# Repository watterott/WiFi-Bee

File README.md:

# WiFi-Bee
XBee footprint compatible WiFi/WLAN Module with Microchip ATWINC1500 WiFi Network Controller.

* [Microchip ATWINC1500](https://www.microchip.com/wwwproducts/en/ATWINC1500) WiFi Network Controller
* Integrated WiFi and IPv4 stack
* SPI interface
* XBee compatible Pinout (3.3V)
* Open-Source and released under the [Creative Commons Attribution Share-Alike License](https://creativecommons.org/licenses/by-sa/4.0/).
* **[Documentation on learn.watterott.com](https://learn.watterott.com)**

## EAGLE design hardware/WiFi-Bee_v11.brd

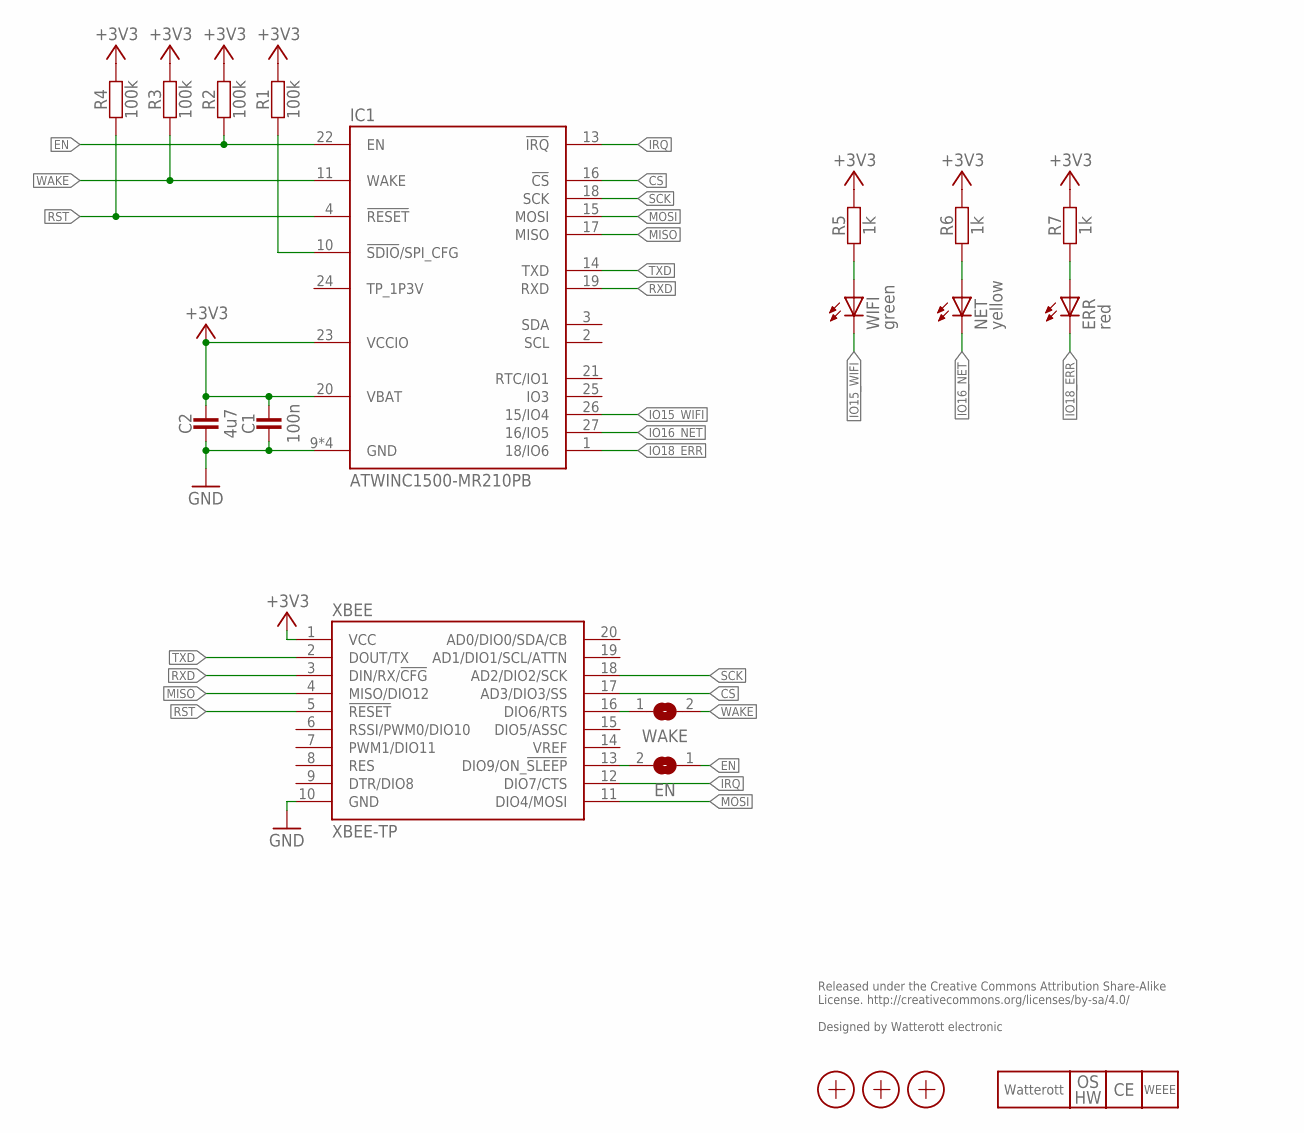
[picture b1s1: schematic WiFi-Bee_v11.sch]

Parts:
C1: 100n; C0402
C2: 4u7; C0402
EN: JUMPER2-0402
ERR: red; C0603
IC1: ATWINC1500-MR210PB; ATWINC1500-MX210
LOGO1: LOGO_CE-2; CE_2MM
LOGO2: LOGO_WEEE-4; WEEE_4MM
LOGO3: LOGO_SPARK-2; SPARK_2MM
LOGO4: LOGO_OSHW-2; OSHW_2MM
NET: yellow; C0603
R1, R2, R3, R4: 100k; C0402
R5, R6, R7: 1k; C0402
WAKE: JUMPER2-0402
WIFI: green; C0603
X1, X2, X3: PASSER-07; PASSER_07MM
XBEE: XBEE-TP; XBEE_TP

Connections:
+3V3: C1.2, C2.2, IC1.20 (VBAT), IC1.23 (VCCIO), R1.2, R2.2, R3.2, R4.2, R5.2, R6.2, R7.2, XBEE.1 (VCC)
CFG: IC1.10 (!SDIO!/SPI_CFG), R1.1
CS: IC1.16 (!CS), XBEE.17 (AD3/DIO3/SS)
EN: EN.1, IC1.22 (EN), R2.1
EN2: EN.2, XBEE.13 (DIO9/ON_!SLEEP!)
GND: C1.1, C2.1, IC1.9 (GND), IC1.12 (GND), IC1.28 (GND), IC1.GND, XBEE.10 (GND)
IO15_WIFI: IC1.26 (15/IO4), WIFI.C
IO16_NET: IC1.27 (16/IO5), NET.C
IO18_ERR: ERR.C, IC1.1 (18/IO6)
IRQ: IC1.13 (!IRQ), XBEE.12 (DIO7/CTS)
LEDE: ERR.A, R7.1
LEDN: NET.A, R6.1
LEDW: R5.1, WIFI.A
MISO: IC1.17 (MISO), XBEE.4 (MISO/DIO12)
MOSI: IC1.15 (MOSI), XBEE.11 (DIO4/MOSI)
RST: IC1.4 (!RESET), R4.1, XBEE.5 (!RESET!)
RXD: IC1.19 (RXD), XBEE.3 (DIN/RX/!CFG!)
SCK: IC1.18 (SCK), XBEE.18 (AD2/DIO2/SCK)
TXD: IC1.14 (TXD), XBEE.2 (DOUT/TX)
WAKE: IC1.11 (WAKE), R3.1, WAKE.2
WAKE1: WAKE.1, XBEE.16 (DIO6/RTS)

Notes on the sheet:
Released under the Creative Commons Attribution Share-Alike License. http://creativecommons.org/licenses/by-sa/4.0/ Designed by Watterott electronic

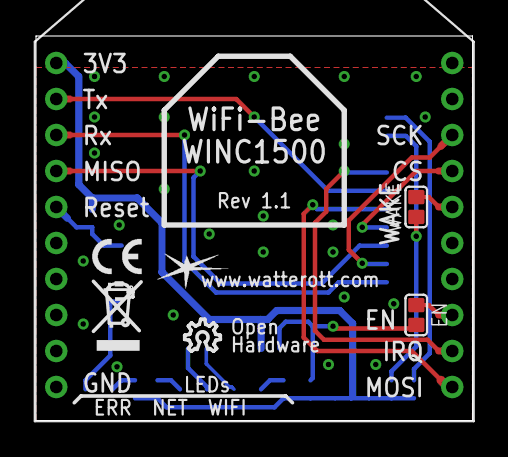
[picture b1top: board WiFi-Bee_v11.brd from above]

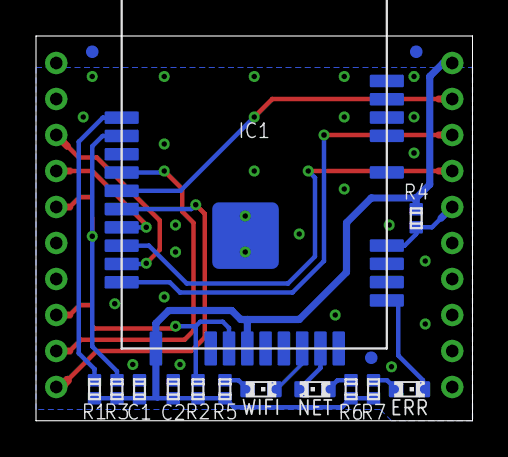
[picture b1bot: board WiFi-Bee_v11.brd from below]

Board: 2 copper layers, 24.2 x 21.4 mm, 23 parts (16 on the bottom side), 21 nets.

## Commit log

2017-09-12 added readme
2018-05-03 updated layout and schematics
2019-05-14 added picture
